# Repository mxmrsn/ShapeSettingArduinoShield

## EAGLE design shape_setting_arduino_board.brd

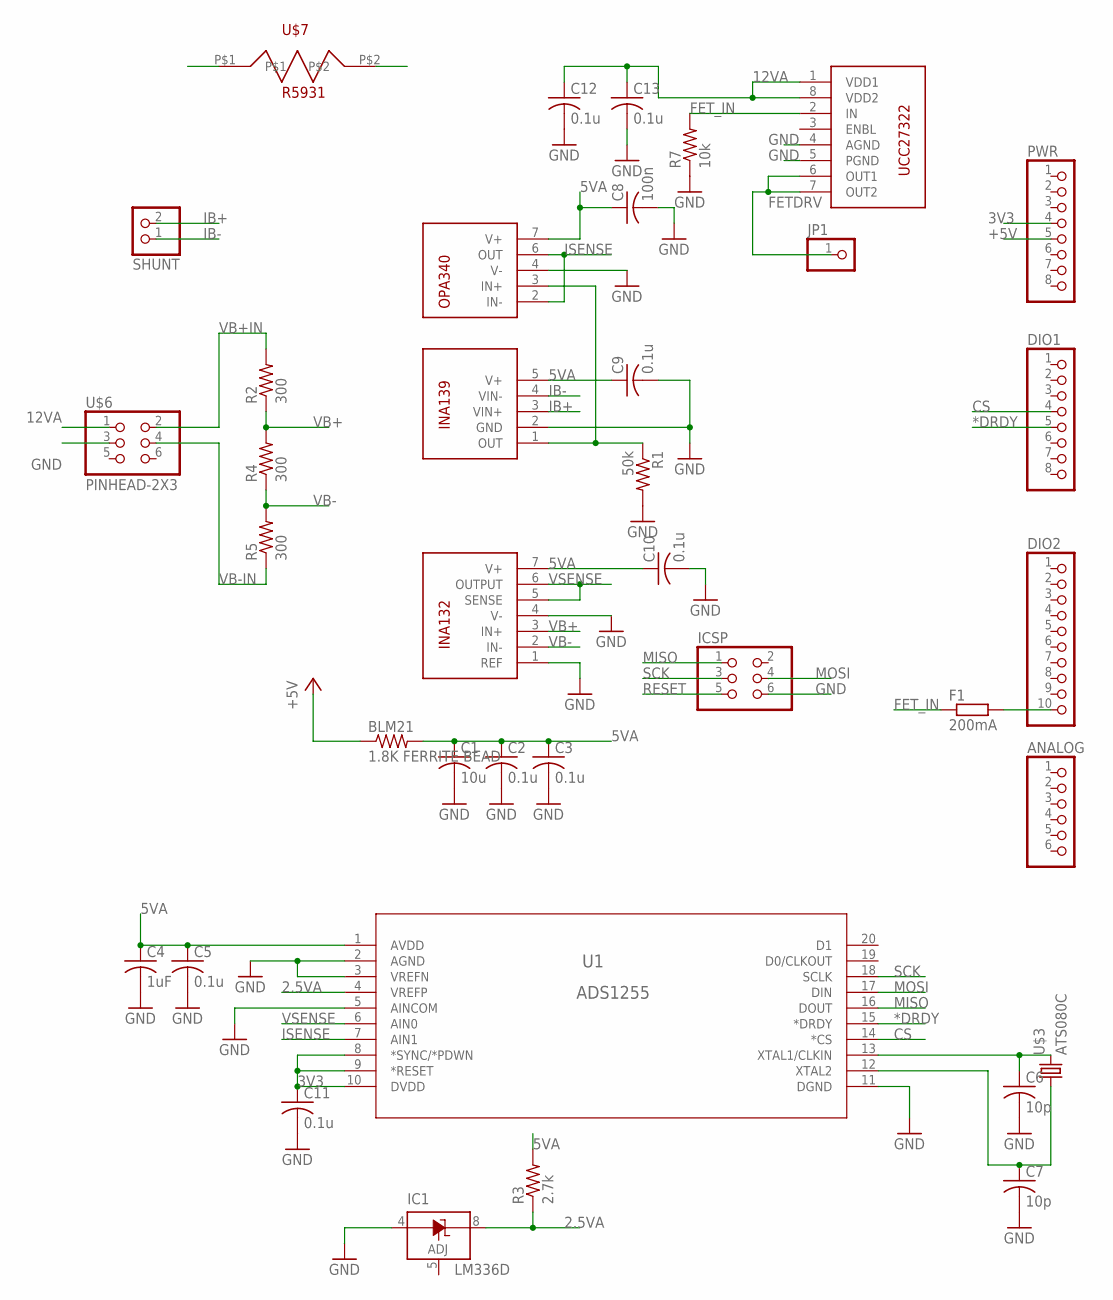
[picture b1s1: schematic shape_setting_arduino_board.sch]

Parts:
ANALOG: PINHD-1X6; 1X06
BLM21: 1.8K FERRITE BEAD; R0805
C1: 10u; C0805
C2, C3, C5, C9, C10, C11, C12, C13: 0.1u; C0603
C4: 1uF; C0805
C6, C7: 10p; C0603
C8: 100n; C0603
DIO1: PINHD-1X8; 1X08
DIO2: PINHD-1X10; 1X10
F1: 200mA; R0603
IC1: LM336D; SO08
ICSP: PINHD-2X3; 2X03
JP1: PINHD-1X1; 1X01
PWR: PINHD-1X8; 1X08
R1: 50k; R0603
R2, R4, R5: 300; R0603
R3: 2.7k; R0603
R7: 10k; R0603
SHUNT: PINHD-1X2; 1X02
U1: ADS1255; DB20
U$1: INA139; SOT-23(DBV)
U$2: INA132U; 8SOIC(D)
U$3: ATS080C; ATS
U$4: OPA340; 8SOIC(D)
U$5: UCC27322; 8SOIC(D)
U$6: PINHEAD-2X3; 2X03
U$7: R5931; 5931

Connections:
2.5VA: IC1.8 (C), R3.1, U1.4 (VREFP)
3V3: C11.1, PWR.4, U1.8 (*SYNC/*PDWN), U1.9 (*RESET), U1.10 (DVDD)
5VA: BLM21.2, C1.1, C2.1, C3.1, C4.1, C5.1, C8.1, C9.1, C10.1, R3.2, U1.1 (AVDD), U$1.5 (V+), U$2.7 (V+), U$4.7 (V+)
12VA: C12.1, C13.1, U$5.1 (VDD1), U$5.8 (VDD2), U$6.1
*DRDY: DIO1.5, U1.15 (*DRDY)
+5V: BLM21.1, PWR.5
CS: DIO1.4, U1.14 (*CS)
FETDRV: JP1.1, U$5.6 (OUT1), U$5.7 (OUT2)
FET_IN: F1.1, R7.2, U$5.2 (IN)
GND: C1.2, C2.2, C3.2, C4.2, C5.2, C6.2, C7.2, C8.2, C9.2, C10.2, C11.2, C12.2, C13.2, IC1.4 (A), ICSP.6, R1.2, R7.1, U1.2 (AGND), U1.3 (VREFN), U1.5 (AINCOM), U1.11 (DGND), U$1.2 (GND), U$2.1 (REF), U$2.4 (V-), U$4.4 (V-), U$5.4 (AGND), U$5.5 (PGND), U$6.3
IB+: SHUNT.2, U$1.3 (VIN+)
IB-: SHUNT.1, U$1.4 (VIN-)
ISENSE: U1.7 (AIN1), U$4.2 (IN-), U$4.6 (OUT)
MISO: ICSP.1, U1.16 (DOUT)
MOSI: ICSP.4, U1.17 (DIN)
unnamed: R1.1, U$1.1 (OUT), U$4.3 (IN+)
unnamed: C6.1, U1.13 (XTAL1/CLKIN), U$3.2
unnamed: C7.1, U1.12 (XTAL2), U$3.1
unnamed: DIO2.10, F1.2
RESET: ICSP.5
SCK: ICSP.3, U1.18 (SCLK)
SENSE+: U$7.P$2
SENSE-: U$7.P$1
VB+: R2.1, R4.2, U$2.3 (IN+)
VB+IN: R2.2, U$6.2
VB-: R4.1, R5.2, U$2.2 (IN-)
VB-IN: R5.1, U$6.4
VSENSE: U1.6 (AIN0), U$2.5 (SENSE), U$2.6 (OUTPUT)

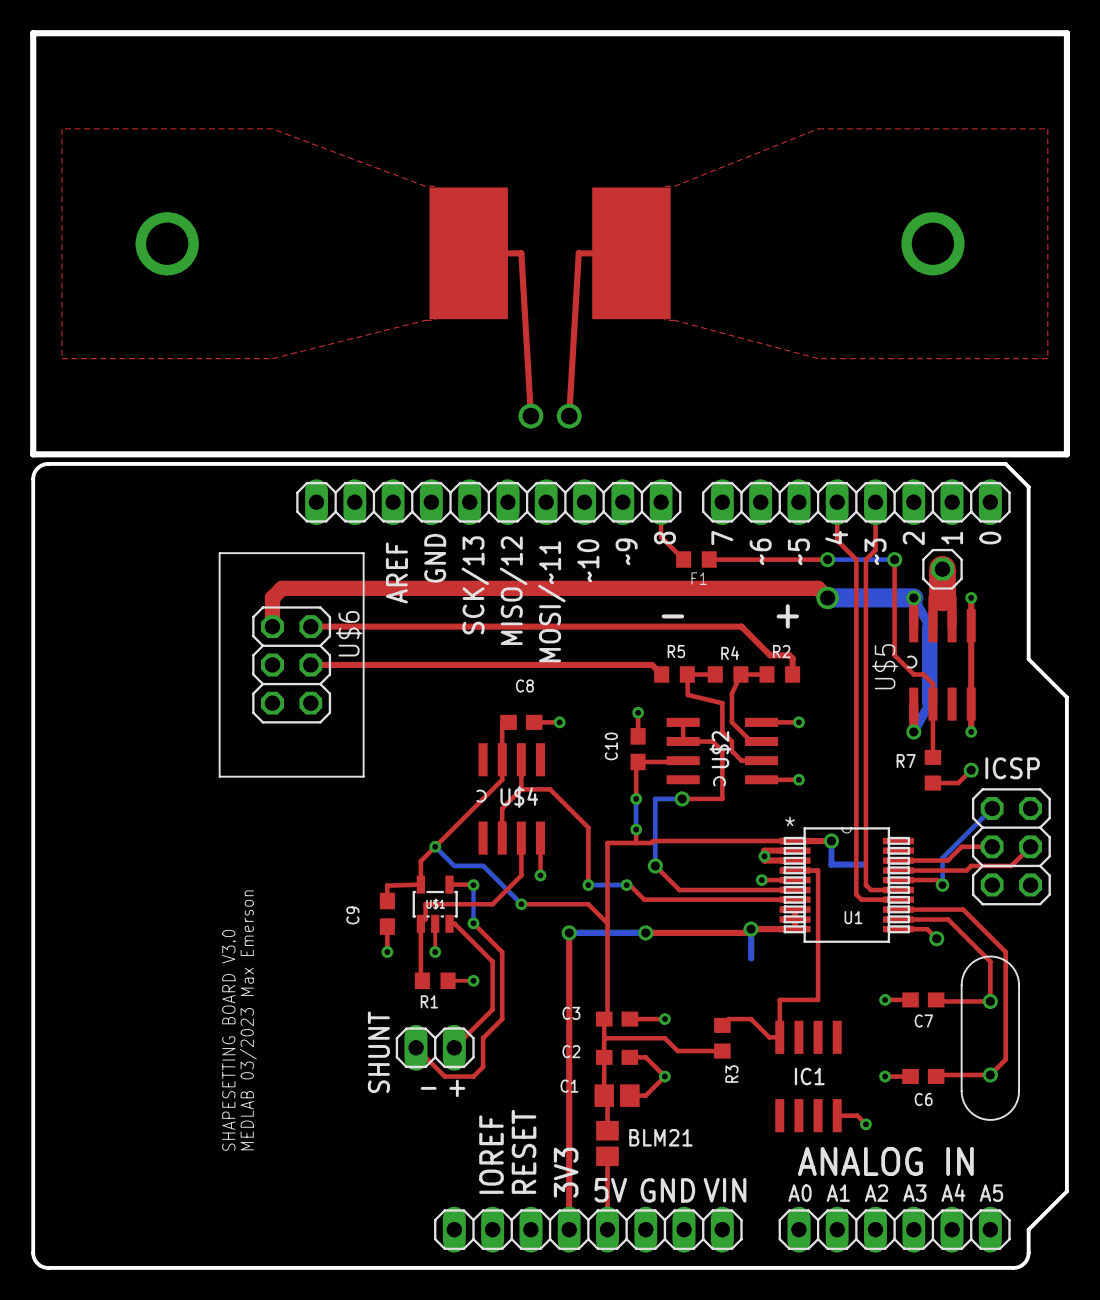
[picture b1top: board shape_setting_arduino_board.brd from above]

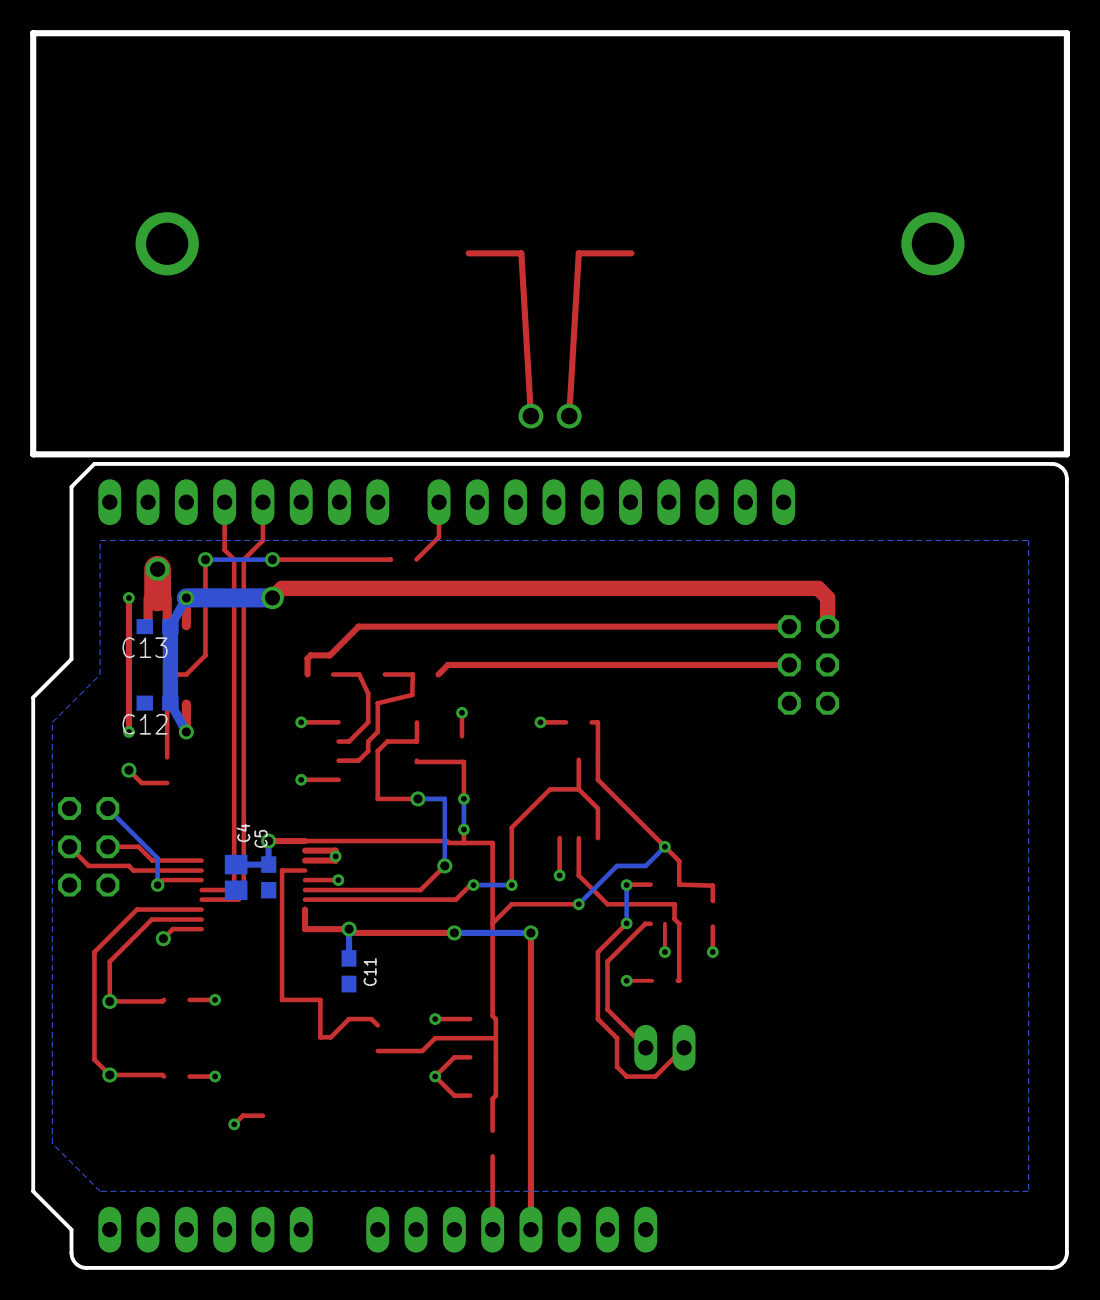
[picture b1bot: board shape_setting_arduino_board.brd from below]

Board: 2 copper layers, 68.6 x 81.8 mm, 37 parts (5 on the bottom side), 25 nets.

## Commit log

2023-03-11 updated label
